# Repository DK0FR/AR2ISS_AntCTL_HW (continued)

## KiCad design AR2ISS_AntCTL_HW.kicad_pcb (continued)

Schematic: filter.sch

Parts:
C51, C52: 470p; C_0603_1608Metric
C53, C54: 1n; C_0603_1608Metric
D12: PSM712-LF-T7; SOT-23_Handsoldering
J13: Conn_01x02; PinHeader_1x02_P2.54mm_Vertical
L22, L23: 74279266; L_0603_1608Metric
L24, L25: 10u; L_0603_1608Metric
R80: 120; R_0603_1608Metric
R85, R86: 220; R_0603_1608Metric

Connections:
/RS422/RS485Tranceiver1/A_in: D12.1 (A1), L23.2, R80.1; also elsewhere on the board
/RS422/RS485Tranceiver1/B_in: D12.2 (A2), J13.2, L22.2; also elsewhere on the board
/RS422/RS485Tranceiver1/filter/A_Out: L24.1; also elsewhere on the board
/RS422/RS485Tranceiver1/filter/B_Out: L25.1; also elsewhere on the board
GND: C51.2, C52.2, C53.2, C54.2, D12.3 (common); also elsewhere on the board
unnamed: C51.1, L22.1, L24.2, R85.1
unnamed: C52.1, L23.1, L25.2, R86.1
unnamed: C53.1, R85.2
unnamed: C54.1, R86.2
unnamed: J13.1, R80.2

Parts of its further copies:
C36, C37, C41, C42, C46, C47: 470p; C_0603_1608Metric
C38, C39, C43, C44, C48, C49: 1n; C_0603_1608Metric
D9, D10, D11: PSM712-LF-T7; SOT-23_Handsoldering
J10, J11, J12: Conn_01x02; PinHeader_1x02_P2.54mm_Vertical
L10, L11, L14, L15, L18, L19: 74279266; L_0603_1608Metric
L12, L13, L16, L17, L20, L21: 10u; L_0603_1608Metric
R31, R66, R73: 120; R_0603_1608Metric
R64, R65, R71, R72, R78, R79: 220; R_0603_1608Metric

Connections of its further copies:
/RS422/RS485Tranceiver2/A_in: D11.1 (A1), L19.2, R73.1; also elsewhere on the board
/RS422/RS485Tranceiver2/B_in: D11.2 (A2), J12.2, L18.2; also elsewhere on the board
/RS422/RS485Tranceiver2/filter/A_Out: L20.1; also elsewhere on the board
/RS422/RS485Tranceiver2/filter/B_Out: L21.1; also elsewhere on the board
/RS422/RS485Tranceiver3/A_in: D9.1 (A1), L11.2, R31.1; also elsewhere on the board
/RS422/RS485Tranceiver3/B_in: D9.2 (A2), J10.2, L10.2; also elsewhere on the board
/RS422/RS485Tranceiver3/filter/A_Out: L12.1; also elsewhere on the board
/RS422/RS485Tranceiver3/filter/B_Out: L13.1; also elsewhere on the board
/RS422/RS485Tranceiver4/A_in: D10.1 (A1), L15.2, R66.1; also elsewhere on the board
/RS422/RS485Tranceiver4/B_in: D10.2 (A2), J11.2, L14.2; also elsewhere on the board
/RS422/RS485Tranceiver4/filter/A_Out: L16.1; also elsewhere on the board
/RS422/RS485Tranceiver4/filter/B_Out: L17.1; also elsewhere on the board
GND: C36.2, C37.2, C38.2, C39.2, C41.2, C42.2, C43.2, C44.2, C46.2, C47.2, C48.2, C49.2, D9.3 (common), D10.3 (common), D11.3 (common); also elsewhere on the board
unnamed: C36.1, L10.1, L12.2, R64.1
unnamed: C37.1, L11.1, L13.2, R65.1
unnamed: C38.1, R64.2
unnamed: C39.1, R65.2
unnamed: C41.1, L14.1, L16.2, R71.1
unnamed: C42.1, L15.1, L17.2, R72.1
unnamed: C43.1, R71.2
unnamed: C44.1, R72.2
unnamed: C46.1, L18.1, L20.2, R78.1
unnamed: C47.1, L19.1, L21.2, R79.1
unnamed: C48.1, R78.2
unnamed: C49.1, R79.2
unnamed: J10.1, R31.2
unnamed: J11.1, R66.2
unnamed: J12.1, R73.2

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
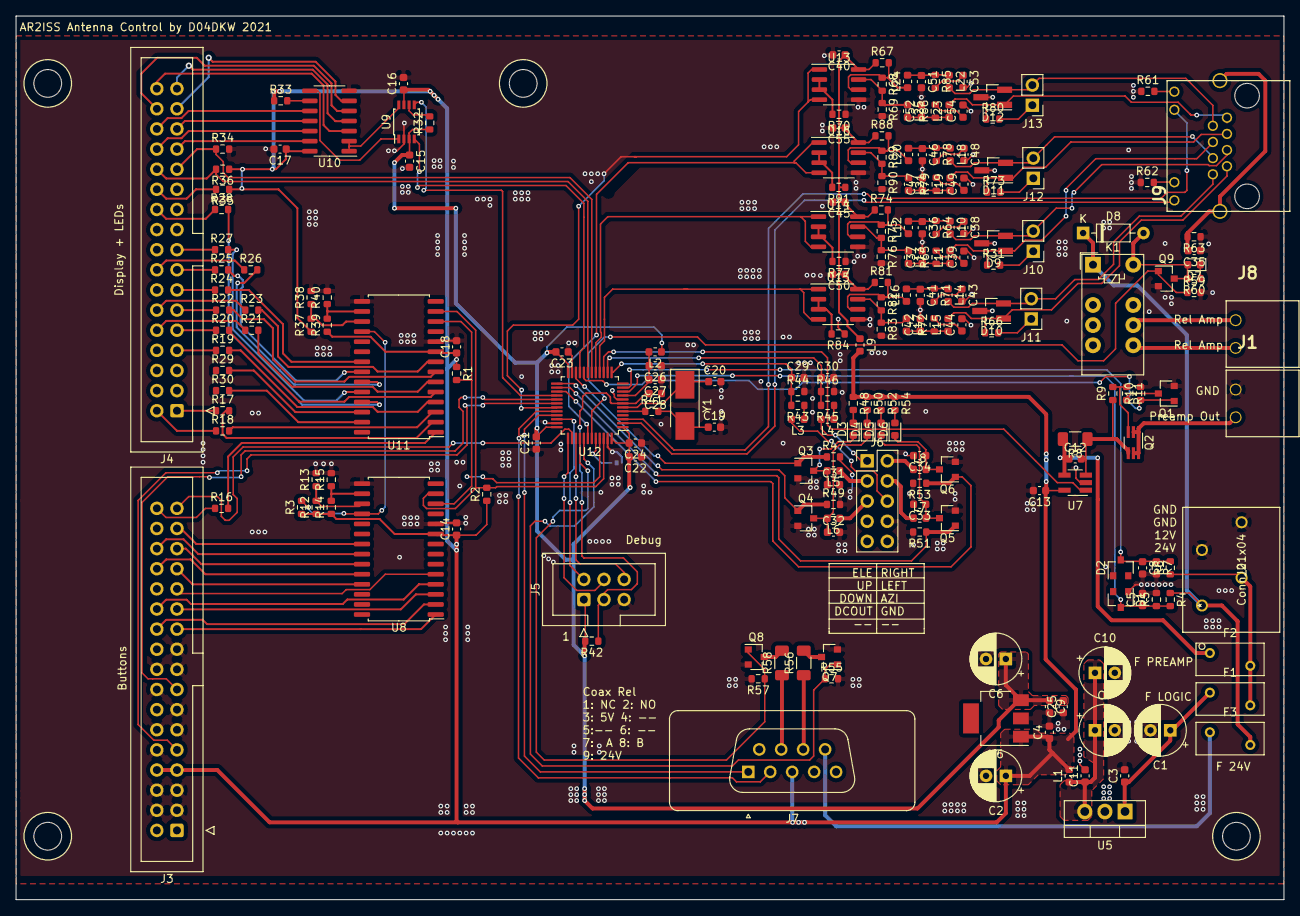
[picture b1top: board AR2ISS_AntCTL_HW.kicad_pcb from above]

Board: 2 copper layers, 160.0 x 111.5 mm, 226 parts (1 on the bottom side), 176 nets.

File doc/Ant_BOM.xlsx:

Designator | Quantity | Value | Footprint | LCSC Part #
C1 C2 C6 C7 C10 | 5 | 22u | Capacitor_THT:CP_Radial_D6.3mm_P2.50mm
C19 C20 | 2 | 16p | Capacitor_SMD:C_0603_1608Metric
C26 C31 C32 C33 C34 C38 C39 C43 C44 C48 C49 C53 C54 | 13 | 1n | Capacitor_SMD:C_0603_1608Metric | C1588
C36 C37 C41 C42 C46 C47 C51 C52 | 8 | 470p | Capacitor_SMD:C_0603_1608Metric | C1620
C3 C4 C5 C8 C9 C11 C12 C13 C14 C15 C16 C17 C18 C21 C22 C23 C24 C25 C27 C28 C29 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 | 27 | 100n | Capacitor_SMD:C_0603_1608Metric | C14663
D1 D2 | 2 | BZX84Cxx | Diode_SMD:D_SOT-23_ANK
D3 D4 D5 D6 D7 | 5 | LED | Diode_SMD:D_0603_1608Metric | C2286
D8 | 1 | 1N4148 | Diode_THT:D_DO-35_SOD27_P7.62mm_Horizontal | 1N4148
D9 D10 D11 D12 | 4 | PESD2CAN | Package_TO_SOT_SMD:SOT-23_Handsoldering | C32677
F1 F2 F3 | 3 | PFRA 050 | Fuse:Fuse_BelFuse_0ZRE0005FF_L8.3mm_W3.8mm | PFRA.050
J1 J8 | 2 | Conn_01x02 | stmbl:RM3.5_1x2
J10 J11 J12 J13 | 4 | Conn_01x02 | Connector_PinHeader_2.54mm:PinHeader_1x02_P2.54mm_Vertical
J2 | 1 | Conn_01x04 | AR2ISS:250-204
J3 J4 | 2 | Conn_02x17_Odd_Even | Connector_IDC:IDC-Header_2x17_P2.54mm_Vertical | C358757
J5 | 1 | Conn_02x03_Odd_Even | Connector_IDC:IDC-Header_2x03_P2.54mm_Vertical
J6 | 1 | Conn_01x10 | Connector_PinHeader_2.54mm:PinHeader_2x05_P2.54mm_Vertical
J7 | 1 | DB9_Female | Connector_Dsub:DSUB-9_Female_Vertical_P2.77x2.84mm
J9 | 1 | RJ45_LED | stmbl:RJ45_LED
JP1 | 1 | Jumper_NC_Small | Jumper:SolderJumper-2_P1.3mm_Bridged_RoundedPad1.0x1.5mm
K1 | 1 | G6S-2 | Relay_THT:Relay_DPDT_Omron_G6S-2 | G6S-2G-Y DC12
L1 L2 L9 | 3 | L | Inductor_SMD:L_0603_1608Metric | BLM18KG102SN1D
L10 L11 L14 L15 L18 L19 L22 L23 | 8 | 74279266 | Inductor_SMD:L_0603_1608Metric | C85824
L12 L13 L16 L17 L20 L21 L24 L25 | 8 | 10u | Inductor_SMD:L_0603_1608Metric | C1035
L3 L4 L5 L6 L7 L8 | 6 | 2.2u | Inductor_SMD:L_0603_1608Metric | C1034
Q1 Q3 Q4 Q5 Q6 Q7 Q8 Q9 | 8 | AO3400A | Package_TO_SOT_SMD:SOT-23 | C344010
Q2 | 1 | SI1443EDH | Package_SO:SO-8_5.3x6.2mm_P1.27mm | SI1443EDH-T1-BE3
R1 R2 R3 R5 R32 R60 R70 R77 R84 R91 | 10 | 3k | Resistor_SMD:R_0603_1608Metric | C4211
R10 R47 R49 R51 R53 R55 R57 R59 | 8 | 100k | Resistor_SMD:R_0603_1608Metric | C25803
R12 R13 R14 R15 R37 R38 R39 R40 | 8 | R | Resistor_SMD:R_0603_1608Metric
R16 R17 R18 R19 R20 R21 R22 R23 R24 R25 R26 R27 R28 R29 R30 R48 R50 R52 R54 R64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 | 27 | 220 | Resistor_SMD:R_0603_1608Metric | C22962
R31 R66 R73 R80 | 4 | 120 | Resistor_SMD:R_0603_1608Metric | C22787
R4 | 1 | 33k | Resistor_SMD:R_0603_1608Metric | C4216
R41 | 1 | 0 | Resistor_SMD:R_0603_1608Metric | C21189
R43 R45 | 2 | 4.7k | Resistor_SMD:R_0603_1608Metric | C23162
R44 R46 | 2 | 9.1k | Resistor_SMD:R_0603_1608Metric | C23260
R56 R58 | 2 | 50 | Resistor_SMD:R_1206_3216Metric_Pad1.30x1.75mm_HandSolder | C17958
R6 | 1 | 6.2k | Resistor_SMD:R_0603_1608Metric | C4260
R7 R11 R61 R62 R63 | 9 | 1k | Resistor_SMD:R_0603_1608Metric | C21190
R8 | 1 | 0.1 | Resistor_SMD:R_1206_3216Metric_Pad1.30x1.75mm_HandSolder | KDV12DR100ET
R9 R33 R34 R35 R36 R42 | 14 | 10k | Resistor_SMD:R_0603_1608Metric | C25804
U1 U2 U3 U4 | 4 | non_plated | stmbl:non_plated_3mm
U10 | 1 | 74HC164 | Package_SO:SOIC-14_3.9x8.7mm_P1.27mm | C6825
U12 | 1 | STM32L522CCTx | Package_QFP:LQFP-48_7x7mm_P0.5mm
U13 U14 U15 U16 | 4 | SN65HVD3082 | Package_SO:SOIC-8_3.9x4.9mm_P1.27mm | C8963
U5 | 1 | LME78_05-1.0 | Package_TO_SOT_THT:TO-220-3_Vertical | TSR 1-2450E
U6 | 1 | L78033 | Package_TO_SOT_SMD:SOT-223 | UA78M33CDCYR
U7 | 1 | TSC101B | Package_TO_SOT_SMD:SOT-23-5_HandSoldering | TSC101BIYLT
U8 U11 | 2 | MCP23017_SO | Package_SO:SOIC-28W_7.5x17.9mm_P1.27mm | C47023
U9 | 1 | TXB0102DCT | Package_SO:TSSOP-8_3x3mm_P0.65mm | NTB0102DP-Q100H
Y1 | 1 | 8M | Crystal:Crystal_SMD_5032-2Pin_5.0x3.2mm_HandSoldering | C115962

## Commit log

2021-03-28 inital commit
2021-04-01 started schematic
2021-04-02 added display pinout
2021-04-02 added rj45 input
2021-04-03 Ready for layout
2021-04-10 first layout
2021-04-19 updated RS422
2021-04-21 copy layout
2021-05-03 rx tx fix, filter mirrored
    switched rx/tx signals
    filters were mirrored
2021-05-13 ready for ordering
2021-05-16 silkscreen
2021-05-20 ready for jlc
2021-10-16 uart rx tx reversed
